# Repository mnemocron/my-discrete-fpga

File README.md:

# Discrete 7400 logic based FPGA
A custom, modular FPGA architecture simulated in VHDL (GHDL), realized with discrete 7400-logic ICs, layouted on PCB with KiCAD and programmed through an abstraction layer via Arduino.

---

Read the full thorugh process and many explanations on my blog: 
[mnemocron.github.io](https://mnemocron.github.io/2023-12-08-DIY-FPGA-diary-0/)

## Motivation

> Why build arguably the worst FPGA ever?

Ever since building Ben Eaters [8 bit CPU](https://eater.net/8bit) myself, I wanted to build something even crazier.
The 8 bit CPU is arguably the worst CPU ever built - but it is a fantastic educational example.
And that is the case for the **4 bit FPGA**. It is a purely educational side project that boosted my knowledge about FPGA architecture, VHDL design and verification. Without further ado, here it is.

## Build Process

The actual part list is WIP. Expected material cost are approximately 50 USD per assembled tile (4:4 bit LUT with interconnect).

---

## Start Here!

Do you want to build this FPGA yourself? Great! Everything, I made regarding this project is in this repository.

To understand the architecture start with `./architecture` or read about it on my blog.
Next, you may dive into the VHDL simulations in `./vhdl` and try out a few things.
Head straight to the `./vhdl/test` directory to see examples with the full FPGA architecture (instead of sub units).

- `./architecture` contains conceptual draw.io block diagrams
- `./doc` contains images, notes and tools that may be helpful
- `./ihdl` (WIP) contains ideas and concepts for a "compiler"
- `./kicad` contains **schematics and PCB files** for KiCAD 7.0
- `./sketch` contains Arduino code for testing of assembled PCB hardware and **abstraction layer in C**
- `./vhdl` contains models for 74xx ICs and the **full FPGA architecture for simulation**

---

## "Assemble" code to map onto the FPGA in Arduino

---

## Inspiration & Honorable Mentions

### Build an 8-bit computer from scratch

> I built a programmable 8-bit computer from scratch on breadboards using only simple logic gates. I documented the whole project in a series of YouTube videos and on this web site. Watch this video for an introduction:

on [eater.net](https://eater.net/8bit)

### Build your own FPGA

> Building a microcontroller or CPU out of discrete logic is a popular hobbyist pursuit, and it serves a useful purpose: building a CPU from scratch teaches you a lot about CPU architecture and tradeoffs; it's an interesting and instructive exercise. So, I wondered, wouldn't building an FPGA out of discrete logic be similarly educational? 

on [Nick's Blog](http://blog.notdot.net/2012/10/Build-your-own-FPGA)

on [Hackaday](https://hackaday.com/2012/11/01/discrete-fpga-will-probably-win-the-7400-logic-competition/)

### Princeton Regonfigurable Gate Array

> Build your own FPGA Chip or embedded FPGA IP with Python, and enjoy a fully open-source, auto-generated CAD flow specifically for your custom FPGA.

on [github](https://github.com/PrincetonUniversity/prga)

on [princeton.edu](http://parallel.princeton.edu/prga/)

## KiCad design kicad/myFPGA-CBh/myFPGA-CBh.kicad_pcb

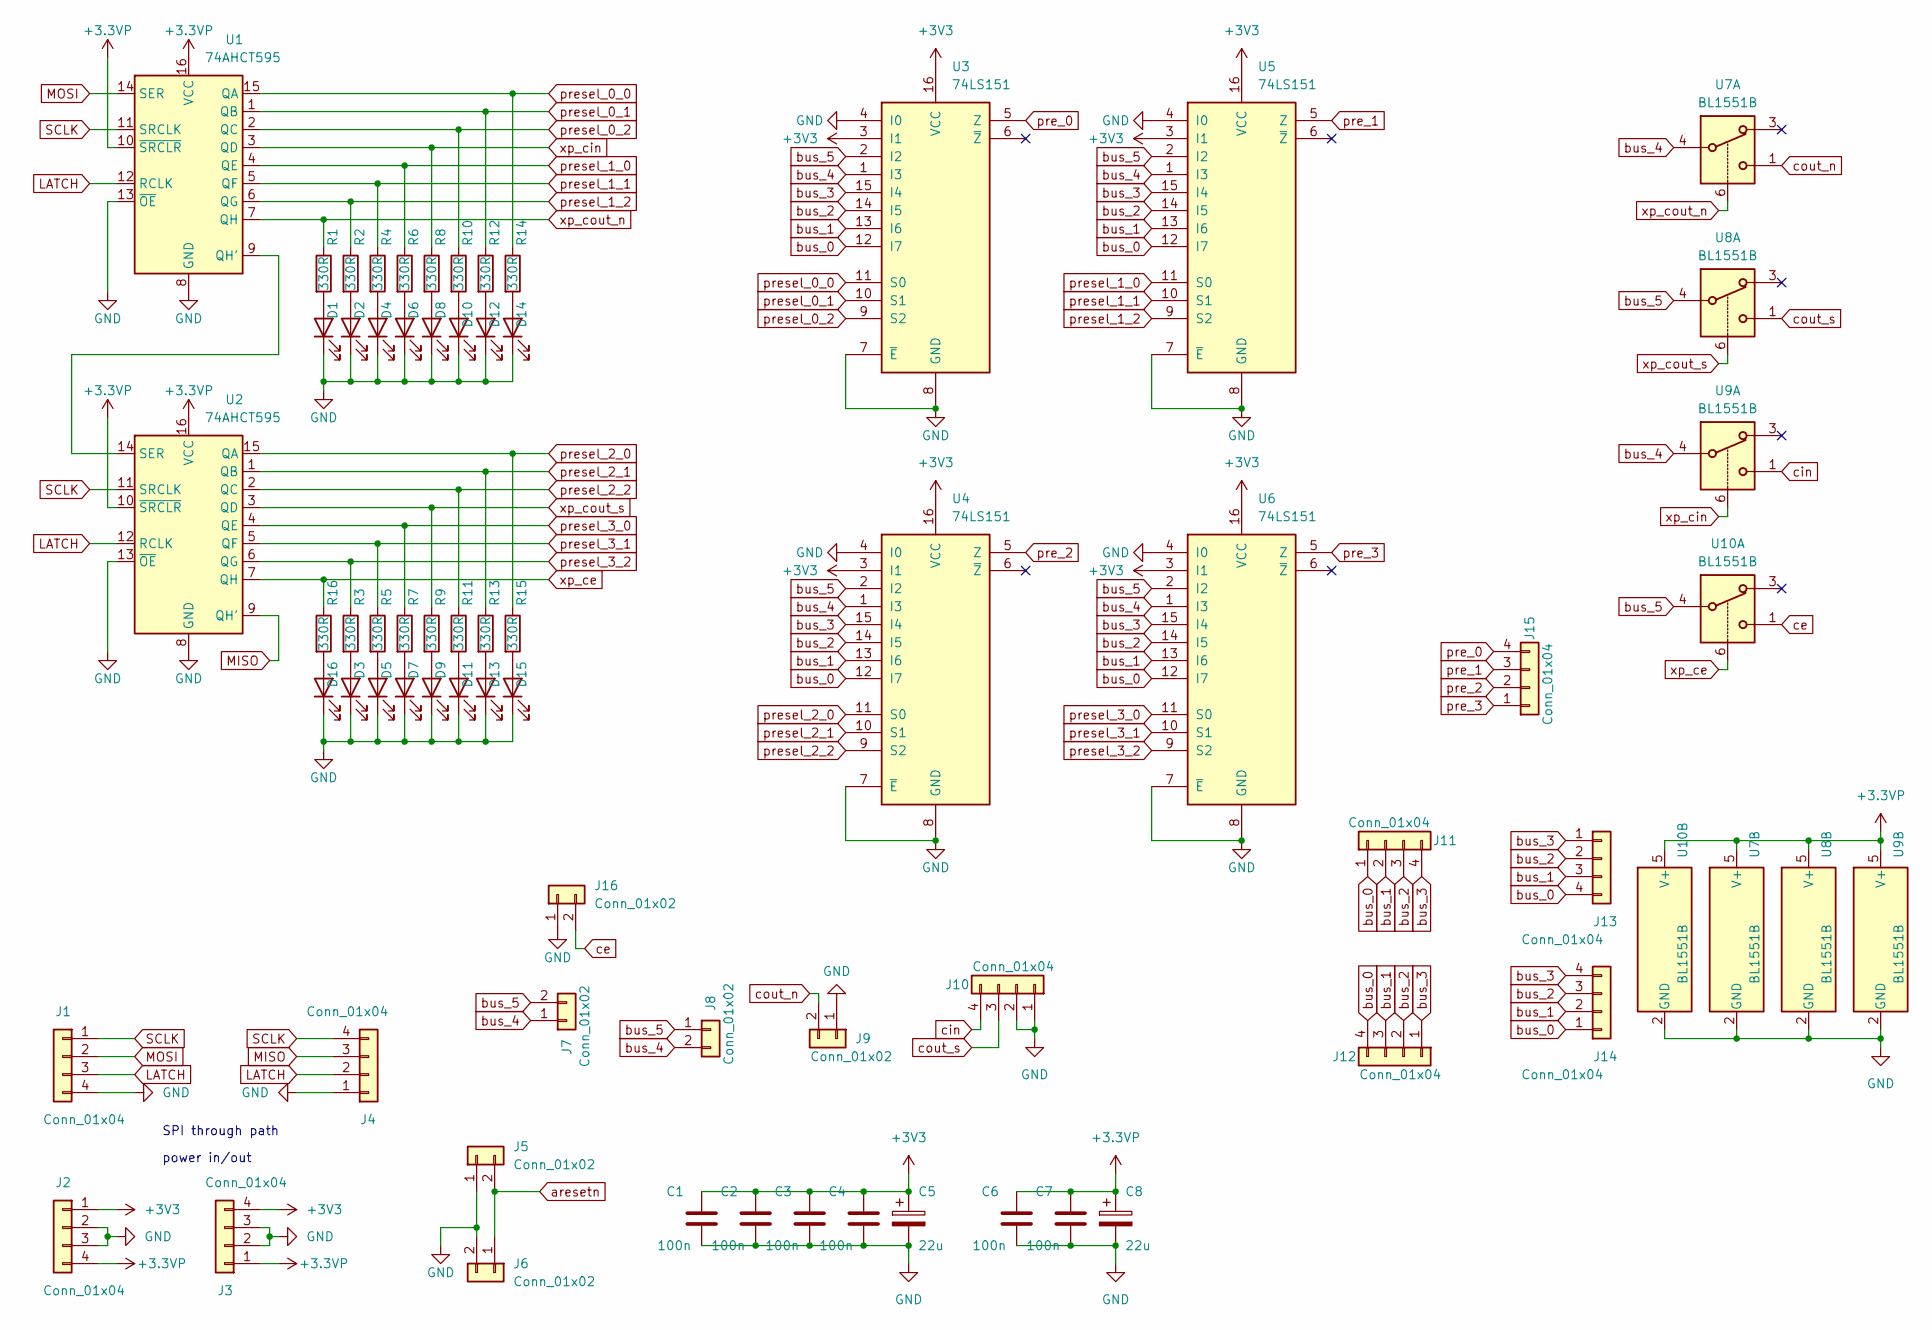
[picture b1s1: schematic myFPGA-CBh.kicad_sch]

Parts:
C1, C2, C3, C4, C6, C7: 100n; C_0603_1608Metric; Voltage 50; Part Nr. CC0603KRX7R9BB104; JLCPCB Part # C14663
C5, C8: 22u; R_1206_3216Metric; Voltage 25; Part Nr. CL31A226KAHNNNE; JLCPCB Part # C12891
D1, D2, D3, D4, D5, D6, D7, D8, D9, D10, D11, D12, D13, D14, D15, D16: LED (green); LED_0805_2012Metric; Part Nr. C2297; JLCPCB Part # C2297
J1, J2, J3, J4, J10, J11, J12, J13, J14, J15: Conn_01x04; PinHeader_1x04_P2.54mm_Horizontal; Part Nr. do not place; JLCPCB Part # do not place
J5, J6, J7, J8, J9, J16: Conn_01x02; PinHeader_1x02_P2.54mm_Horizontal; Part Nr. do not place; JLCPCB Part # do not place
R1, R2, R3, R4, R5, R6, R7, R8, R9, R10, R11, R12, R13, R14, R15, R16: 330R; R_0603_1608Metric; Part Nr. 0603WAF3300T5E; JLCPCB Part # C23138
U1, U2: 74AHCT595; SOIC-16_3.9x9.9mm_P1.27mm; Part Nr. 74HC595D; JLCPCB Part # C5947
U3, U4, U5, U6: 74LS151; SOIC-16_3.9x9.9mm_P1.27mm; Part Nr. 74HC151DR; JLCPCB Part # C6822
U7, U8, U9, U10: BL1551B; SOT-363_SC-70-6; Part Nr. BL1551B; JLCPCB Part # C2944066

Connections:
+3.3VP: C6.1, C7.1, C8.1, J2.4, J3.1, U1.10 (~SRCLR), U1.16 (VCC), U2.10 (~SRCLR), U2.16 (VCC), U7.5 (V+), U8.5 (V+), U9.5 (V+), U10.5 (V+)
+3V3: C1.1, C2.1, C3.1, C4.1, C5.1, J2.1, J3.4, U3.3 (I1), U3.16 (VCC), U4.3 (I1), U4.16 (VCC), U5.3 (I1), U5.16 (VCC), U6.3 (I1), U6.16 (VCC)
GND: C1.2, C2.2, C3.2, C4.2, C5.2, C6.2, C7.2, C8.2, D1.1 (K), D2.1 (K), D3.1 (K), D4.1 (K), D5.1 (K), D6.1 (K), D7.1 (K), D8.1 (K), D9.1 (K), D10.1 (K), D11.1 (K), D12.1 (K), D13.1 (K), D14.1 (K), D15.1 (K), D16.1 (K), J1.4, J2.2, J2.3, J3.2, J3.3, J4.1, J5.1, J6.2, J9.1, J10.1, J10.2, J16.1, U1.8 (GND), U1.13 (~OE), U2.8 (GND), U2.13 (~OE), U3.4 (I0), U3.7 (~E), U3.8 (GND), U4.4 (I0), U4.7 (~E), U4.8 (GND), U5.4 (I0), U5.7 (~E), U5.8 (GND), U6.4 (I0), U6.7 (~E), U6.8 (GND), U7.2 (GND), U8.2 (GND), U9.2 (GND), U10.2 (GND); also elsewhere on the board
LATCH: J1.3, J4.2, U1.12 (RCLK), U2.12 (RCLK); also elsewhere on the board
MISO: J4.3, U2.9 (QH'); also elsewhere on the board
MOSI: J1.2, U1.14 (SER)
unnamed: D1.2 (A), R1.2
unnamed: D2.2 (A), R2.2
unnamed: D3.2 (A), R3.2
unnamed: D4.2 (A), R4.2
unnamed: D5.2 (A), R5.2
unnamed 11: D6.2 (A), R6.2; also elsewhere on the board
unnamed: D7.2 (A), R7.2
unnamed: D8.2 (A), R8.2
unnamed: D9.2 (A), R9.2
unnamed: D10.2 (A), R10.2
unnamed: D11.2 (A), R11.2
unnamed: D12.2 (A), R12.2
unnamed: D13.2 (A), R13.2
unnamed: D14.2 (A), R14.2
unnamed: D15.2 (A), R15.2
unnamed: D16.2 (A), R16.2
unnamed: U1.9 (QH'), U2.14 (SER)
SCLK: J1.1, J4.4, U1.11 (SRCLK), U2.11 (SRCLK); also elsewhere on the board
aresetn: J5.2, J6.1; also elsewhere on the board
bus_0: J11.1, J12.4, J13.4, J14.1, U3.12 (I7), U4.12 (I7), U5.12 (I7), U6.12 (I7)
bus_1: J11.2, J12.3, J13.3, J14.2, U3.13 (I6), U4.13 (I6), U5.13 (I6), U6.13 (I6)
bus_2: J11.3, J12.2, J13.2, J14.3, U3.14 (I5), U4.14 (I5), U5.14 (I5), U6.14 (I5)
bus_3: J11.4, J12.1, J13.1, J14.4, U3.15 (I4), U4.15 (I4), U5.15 (I4), U6.15 (I4)
bus_4: J7.1, J8.2, U3.1 (I3), U4.1 (I3), U5.1 (I3), U6.1 (I3), U7.4, U9.4
bus_5: J7.2, J8.1, U3.2 (I2), U4.2 (I2), U5.2 (I2), U6.2 (I2), U8.4, U10.4
ce: J16.2, U10.1
cin: J10.4, U9.1; also elsewhere on the board
cout_n: J9.2, U7.1
cout_s: J10.3, U8.1; also elsewhere on the board
pre_0: J15.4, U3.5 (Z); also elsewhere on the board
pre_1: J15.3, U5.5 (Z); also elsewhere on the board
pre_2: J15.2, U4.5 (Z); also elsewhere on the board
pre_3: J15.1, U6.5 (Z); also elsewhere on the board
presel_0_0: R14.1, U1.15 (QA), U3.11 (S0)
presel_0_1: R12.1, U1.1 (QB), U3.10 (S1)
presel_0_2: R10.1, U1.2 (QC), U3.9 (S2)
presel_1_0: R6.1, U1.4 (QE), U5.11 (S0); also elsewhere on the board
presel_1_1: R4.1, U1.5 (QF), U5.10 (S1)
presel_1_2: R2.1, U1.6 (QG), U5.9 (S2)
presel_2_0: R15.1, U2.15 (QA), U4.11 (S0)
presel_2_1: R13.1, U2.1 (QB), U4.10 (S1)
presel_2_2: R11.1, U2.2 (QC), U4.9 (S2)
presel_3_0: R7.1, U2.4 (QE), U6.11 (S0)
presel_3_1: R5.1, U2.5 (QF), U6.10 (S1)
presel_3_2: R3.1, U2.6 (QG), U6.9 (S2)
xp_ce: R16.1, U2.7 (QH), U10.6
xp_cin: R8.1, U1.3 (QD), U9.6
xp_cout_n: R1.1, U1.7 (QH), U7.6
xp_cout_s: R9.1, U2.3 (QD), U8.6

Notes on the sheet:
SPI through path
power in/out

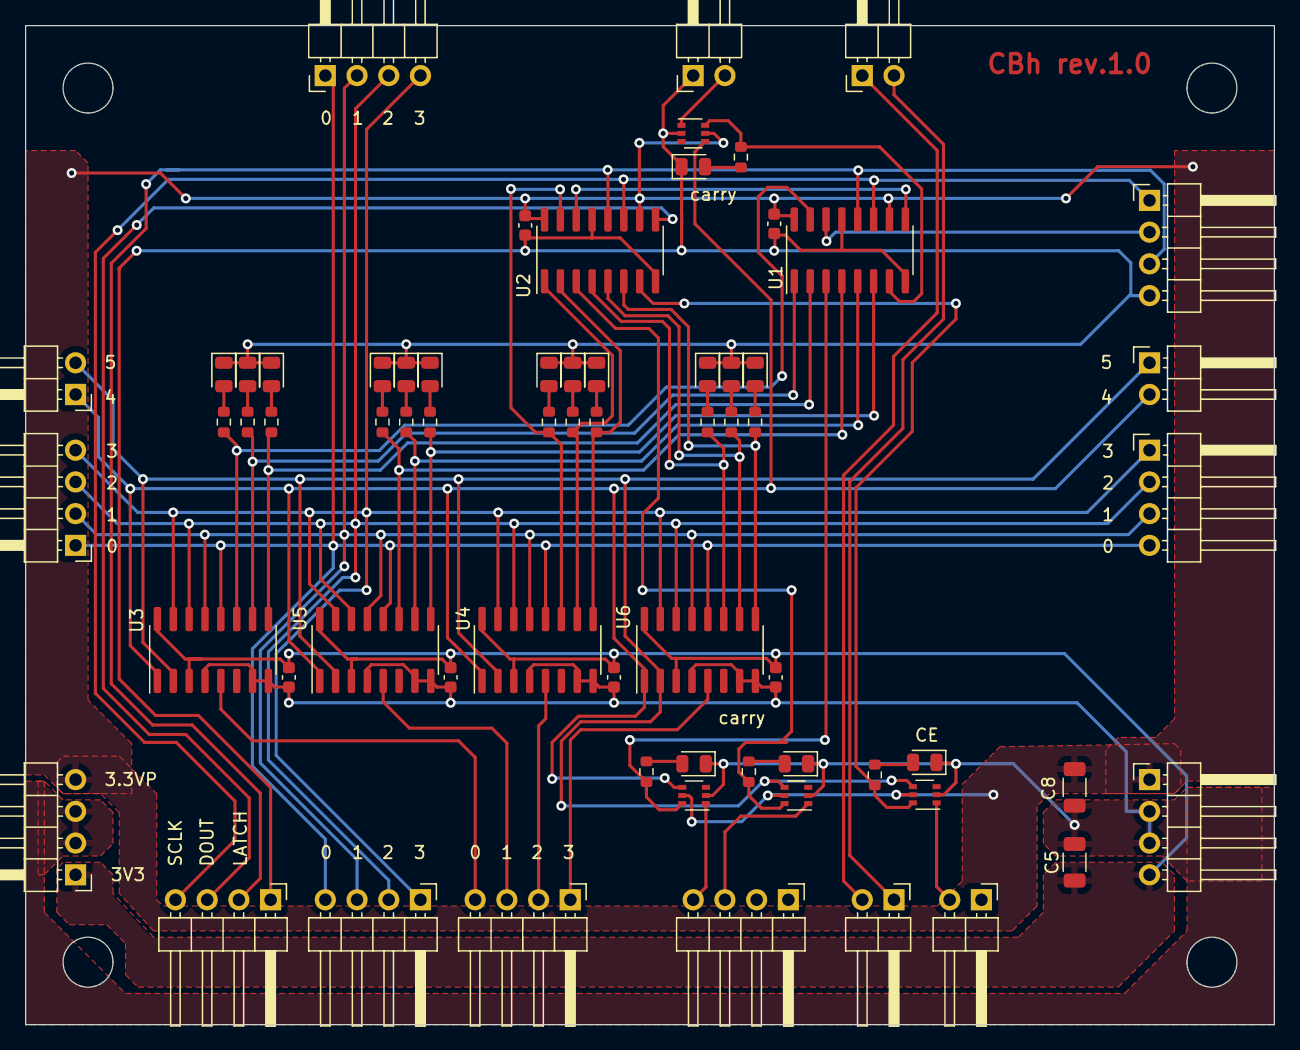
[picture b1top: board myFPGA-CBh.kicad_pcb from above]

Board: 2 copper layers, 100.0 x 80.0 mm, 66 parts (0 on the bottom side), 55 nets.

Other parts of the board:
Re: 330R; R_0603_1608Metric
locked: Conn_01x04; PinHeader_1x04_P2.54mm_Horizontal
locked#2: Conn_01x02; PinHeader_1x02_P2.54mm_Horizontal
locked#3, locked#4: Conn_01x04; PinHeader_1x04_P2.54mm_Horizontal

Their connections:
GND: locked.1, locked.2, locked#2.1, locked#4.1; also elsewhere on the board
LATCH: locked#4.2; also elsewhere on the board
MISO: locked#4.3; also elsewhere on the board
unnamed 11: Re.2; also elsewhere on the board
SCLK: locked#4.4; also elsewhere on the board
aresetn: locked#2.2; also elsewhere on the board
cin: locked.4; also elsewhere on the board
cout_s: locked.3; also elsewhere on the board
pre_0: locked#3.4; also elsewhere on the board
pre_1: locked#3.3; also elsewhere on the board
pre_2: locked#3.2; also elsewhere on the board
pre_3: locked#3.1; also elsewhere on the board
presel_1_0: Re.1; also elsewhere on the board

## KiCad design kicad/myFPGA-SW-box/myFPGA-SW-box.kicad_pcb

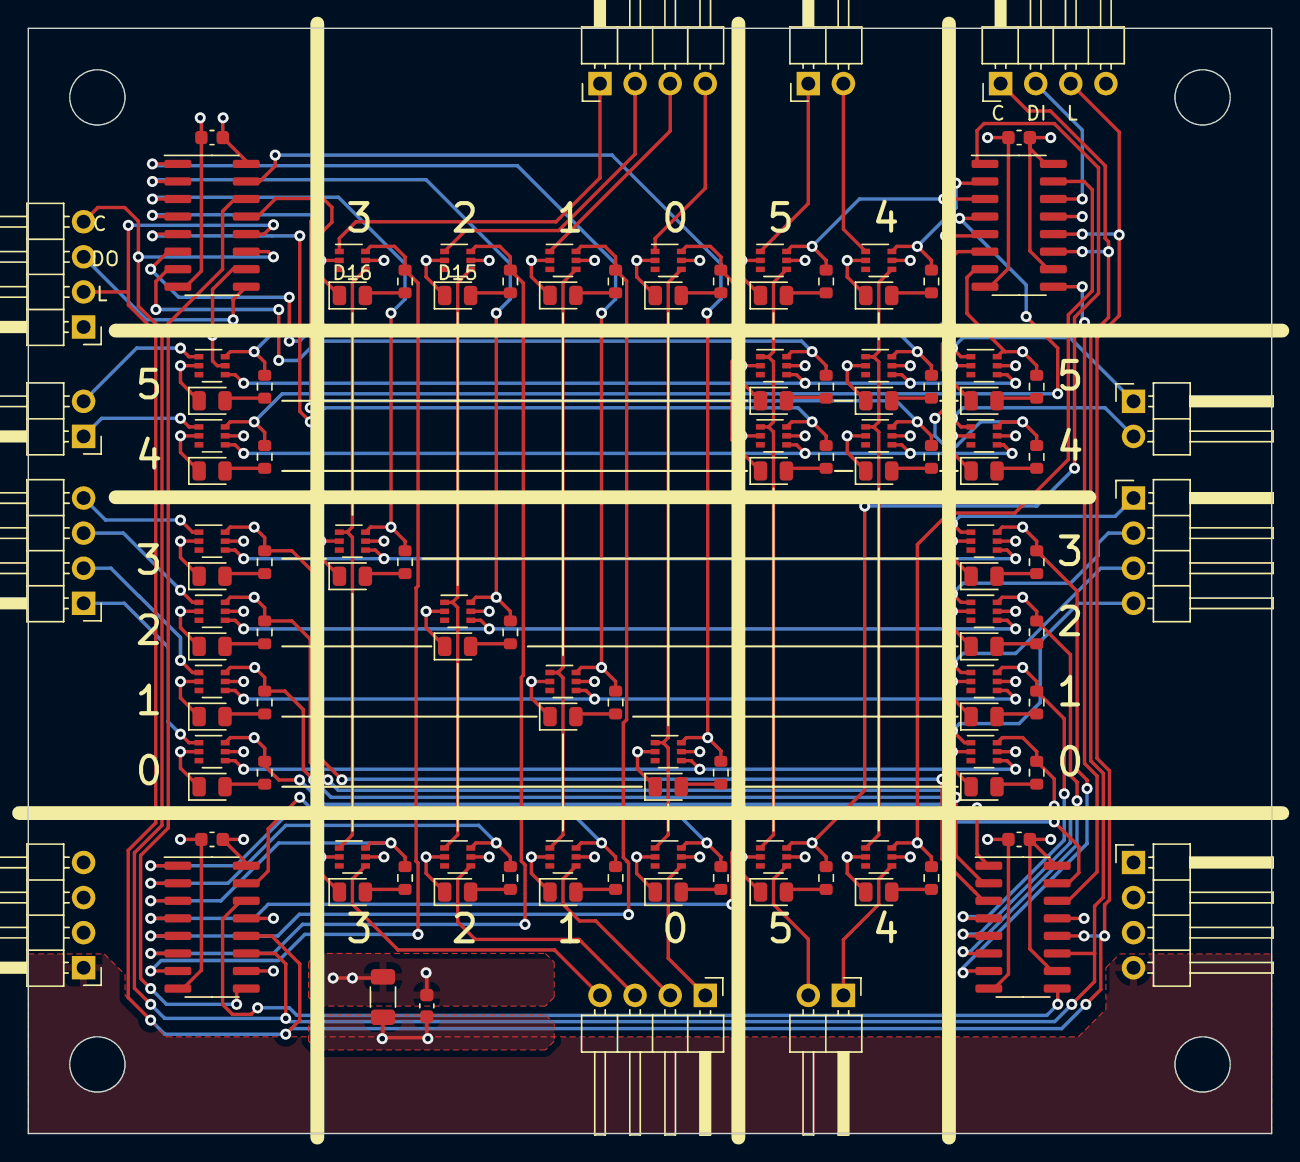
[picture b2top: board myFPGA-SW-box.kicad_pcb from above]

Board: 4 copper layers, 90.0 x 80.0 mm, 118 parts (0 on the bottom side), 110 nets.

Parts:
C1, C2, C3, C4, C5: 100n; C_0603_1608Metric
C6: 22u; R_1206_3216Metric
D1, D2, D3, D4, D5, D6, D7, D8, D9, D10, D11, D12, D13, D14, D15, D16, D17, D18, D19, D20, D21, D22, D23, D24, D25, D26, D27, D28, D29, D30, D31, D32: LED (green); LED_0805_2012Metric
J1, J2, J3, J4, J5, J6, J7, J9: Conn_01x04; PinHeader_1x04_P2.54mm_Horizontal
J8, J10, J11, J12: Conn_01x02; PinHeader_1x02_P2.54mm_Horizontal
R1, R2, R3, R4, R5, R6, R7, R8, R9, R10, R11, R12, R13, R14, R15, R16, R18, R19, R20, R21, R22, R23, R24, R25, R26, R27, R28, R29, R30, R31, R32: 10k; R_0603_1608Metric
Re: 10k; R_0603_1608Metric
U1, U2, U3, U4: 74HC595; SOIC-16_3.9x9.9mm_P1.27mm
U5, U6, U7, U8, U9, U10, U11, U12, U13, U14, U15, U16, U17, U18, U19, U20, U21, U22, U23, U24, U25, U26, U27, U28, U29, U30, U31, U32, U33, U34, U35, U36: NC7SB3157P6X; SOT-363_SC-70-6

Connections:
+3.3VP: C1.1, C2.1, C3.1, C4.1, C5.1, C6.1, J7.4, J9.1, U1.10 (~SRCLR), U1.16 (VCC), U2.10 (~SRCLR), U2.16 (VCC), U3.10 (~SRCLR), U3.16 (VCC), U4.10 (~SRCLR), U4.16 (VCC), U5.5 (V+), U6.5 (V+), U7.5 (V+), U8.5 (V+), U9.5 (V+), U10.5 (V+), U11.5 (V+), U12.5 (V+), U13.5 (V+), U14.5 (V+), U15.5 (V+), U16.5 (V+), U17.5 (V+), U18.5 (V+), U19.5 (V+), U20.5 (V+), U21.5 (V+), U22.5 (V+), U23.5 (V+), U24.5 (V+), U25.5 (V+), U26.5 (V+), U27.5 (V+), U28.5 (V+), U29.5 (V+), U30.5 (V+), U31.5 (V+), U32.5 (V+), U33.5 (V+), U34.5 (V+), U35.5 (V+), U36.5 (V+)
+3V3: J7.1, J9.4
/east_0: J6.4, U24.1
/east_1: J6.3, U23.1
/east_2: J6.2, U22.1
/east_3: J6.1, U21.1
/north_0: J5.4, U19.1
/north_1: J5.3, U16.1
/north_2: J5.2, U13.1
/north_3: J5.1, U10.1
/prio_east_0: J12.2, U36.1
/prio_east_1: J12.1, U35.1
/prio_north_0: J10.2, U31.1
/prio_north_1: J10.1, U27.1
/prio_south_0: J11.1, U34.4
/prio_south_1: J11.2, U30.4
/prio_west_0: J8.1, U26.1
/prio_west_1: J8.2, U25.1
/south_0: J4.1, U20.4
/south_1: J4.2, U17.4
/south_2: J4.3, U14.4
/south_3: J4.4, U11.4
/west_0: J3.1, U8.1
/west_1: J3.2, U7.1
/west_2: J3.3, U6.1
/west_3: J3.4, U5.1
GND: C1.2, C2.2, C3.2, C4.2, C5.2, C6.2, D1.1 (K), D2.1 (K), D3.1 (K), D4.1 (K), D5.1 (K), D6.1 (K), D7.1 (K), D8.1 (K), D9.1 (K), D10.1 (K), D11.1 (K), D12.1 (K), D13.1 (K), D14.1 (K), D15.1 (K), D16.1 (K), D17.1 (K), D18.1 (K), D19.1 (K), D20.1 (K), D21.1 (K), D22.1 (K), D23.1 (K), D24.1 (K), D25.1 (K), D26.1 (K), D27.1 (K), D28.1 (K), D29.1 (K), D30.1 (K), D31.1 (K), D32.1 (K), J1.4, J2.1, J7.2, J7.3, J9.2, J9.3, U1.8 (GND), U1.13 (~OE), U2.8 (GND), U2.13 (~OE), U3.8 (GND), U3.13 (~OE), U4.8 (GND), U4.13 (~OE), U5.2 (GND), U6.2 (GND), U7.2 (GND), U8.2 (GND), U9.2 (GND), U10.2 (GND), U11.2 (GND), U12.2 (GND), U13.2 (GND), U14.2 (GND), U15.2 (GND), U16.2 (GND), U17.2 (GND), U18.2 (GND), U19.2 (GND), U20.2 (GND), U21.2 (GND), U22.2 (GND), U23.2 (GND), U24.2 (GND), U25.2 (GND), U26.2 (GND), U27.2 (GND), U28.2 (GND), U29.2 (GND), U30.2 (GND), U31.2 (GND), U32.2 (GND), U33.2 (GND), U34.2 (GND), U35.2 (GND), U36.2 (GND)
LATCH: J1.3, J2.2, U1.12 (RCLK), U2.12 (RCLK), U3.12 (RCLK), U4.12 (RCLK)
MISO: J2.3, U4.9 (QH')
MOSI: J1.2, U1.14 (SER)
unnamed: D1.2 (A), R1.2
unnamed: D2.2 (A), R2.2
unnamed: D3.2 (A), R3.2
unnamed: D4.2 (A), R4.2
unnamed: D5.2 (A), R5.2
unnamed: D6.2 (A), R6.2
unnamed: D7.2 (A), R7.2
unnamed: D8.2 (A), R8.2
unnamed: D9.2 (A), R9.2
unnamed: D10.2 (A), R10.2
unnamed: D11.2 (A), R11.2
unnamed: D12.2 (A), R12.2
unnamed: D13.2 (A), R13.2
unnamed: D14.2 (A), R14.2
unnamed: D15.2 (A), R15.2
unnamed: D16.2 (A), R16.2
unnamed: D17.2 (A), Re.2
unnamed: D18.2 (A), R18.2
unnamed: D19.2 (A), R19.2
unnamed: D20.2 (A), R20.2
unnamed: D21.2 (A), R21.2
unnamed: D22.2 (A), R22.2
unnamed: D23.2 (A), R23.2
unnamed: D24.2 (A), R24.2
unnamed: D25.2 (A), R25.2
unnamed: D26.2 (A), R26.2
unnamed: D27.2 (A), R27.2
unnamed: D28.2 (A), R28.2
unnamed: D29.2 (A), R29.2
unnamed: D30.2 (A), R30.2
unnamed: D31.2 (A), R31.2
unnamed: D32.2 (A), R32.2
unnamed: U1.9 (QH'), U2.14 (SER)
unnamed: U2.9 (QH'), U3.14 (SER)
unnamed: U3.9 (QH'), U4.14 (SER)
unnamed: U9.1, U10.4, U11.1
unnamed: U12.1, U13.4, U14.1
unnamed: U6.4, U12.4, U22.4
unnamed: U15.1, U16.4, U17.1
unnamed: U7.4, U15.4, U23.4
unnamed: U18.1, U19.4, U20.1
unnamed: U8.4, U18.4, U24.4
unnamed: U5.4, U9.4, U21.4
unnamed: U25.4, U28.4, U32.4, U35.4
unnamed: U26.4, U29.4, U33.4, U36.4
unnamed: U27.4, U28.1, U29.1, U30.1
unnamed: U31.4, U32.1, U33.1, U34.1
SCLK: J1.1, J2.4, U1.11 (SRCLK), U2.11 (SRCLK), U3.11 (SRCLK), U4.11 (SRCLK)
sw_8: R9.1, U3.15 (QA), U20.6
sw_9: R10.1, U3.1 (QB), U17.6
sw_10: R11.1, U3.2 (QC), U14.6
sw_11: R12.1, U3.3 (QD), U11.6
sw_12: R13.1, U3.4 (QE), U19.6
sw_13: R14.1, U3.5 (QF), U16.6
sw_14: R15.1, U3.6 (QG), U13.6
sw_15: R16.1, U3.7 (QH), U10.6
sw_16: R25.1, U2.15 (QA), U8.6
sw_17: R26.1, U2.1 (QB), U7.6
sw_18: R27.1, U2.2 (QC), U6.6
sw_19: R28.1, U2.3 (QD), U5.6
sw_20: R29.1, U2.4 (QE), U24.6
sw_21: R30.1, U2.5 (QF), U23.6
sw_22: R31.1, U2.6 (QG), U22.6
sw_23: R32.1, U2.7 (QH), U21.6
sw_24: Re.1, U1.15 (QA), U34.6
sw_25: R18.1, U1.1 (QB), U30.6
sw_26: R19.1, U1.2 (QC), U31.6
sw_27: R20.1, U1.3 (QD), U27.6
sw_28: R21.1, U1.4 (QE), U26.6
sw_29: R22.1, U1.5 (QF), U25.6
sw_30: R23.1, U1.6 (QG), U36.6
sw_31: R24.1, U1.7 (QH), U35.6
xp_0: R1.1, U4.15 (QA), U18.6
xp_1: R2.1, U4.1 (QB), U15.6
xp_2: R3.1, U4.2 (QC), U12.6
xp_3: R4.1, U4.3 (QD), U9.6
xp_4: R5.1, U4.4 (QE), U33.6
xp_5: R6.1, U4.5 (QF), U29.6
xp_6: R7.1, U4.6 (QG), U32.6
xp_7: R8.1, U4.7 (QH), U28.6

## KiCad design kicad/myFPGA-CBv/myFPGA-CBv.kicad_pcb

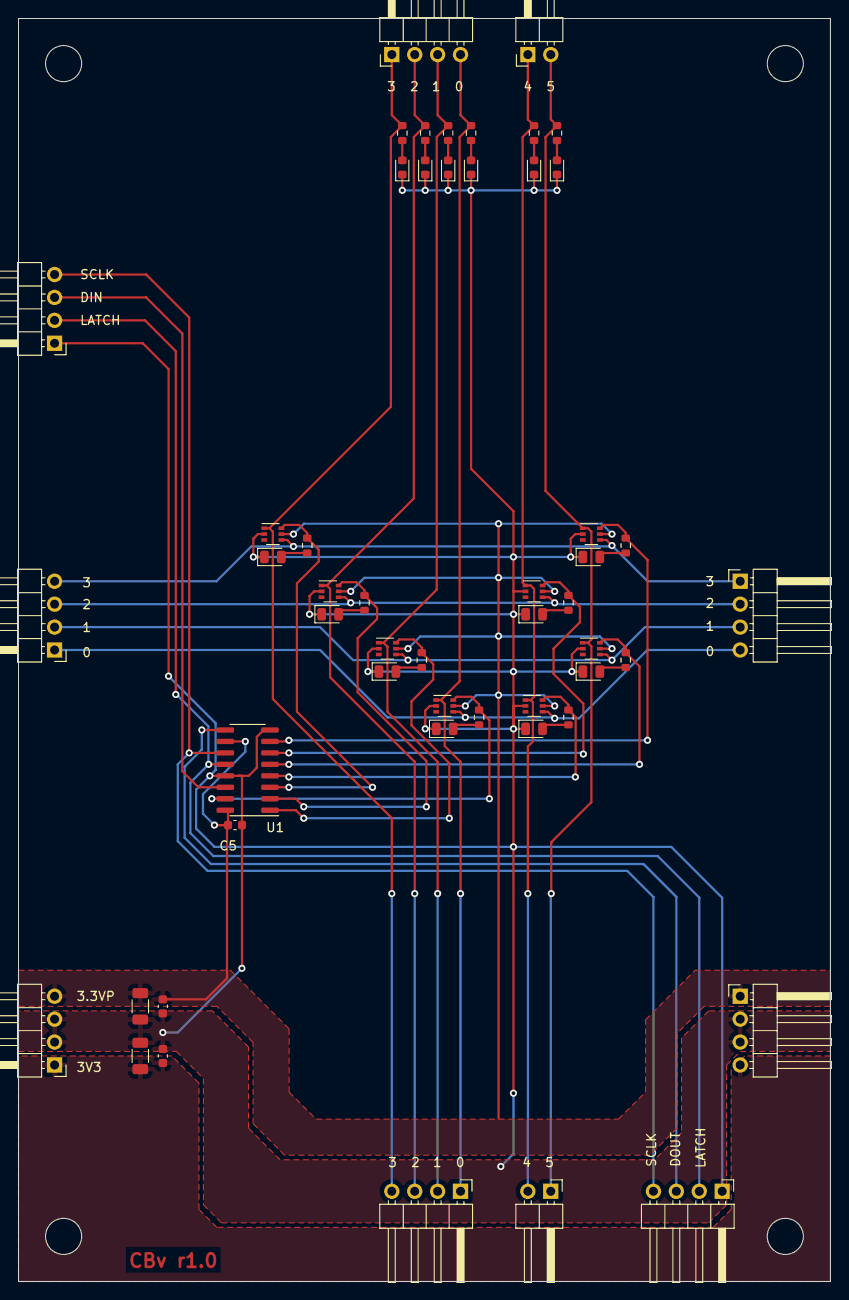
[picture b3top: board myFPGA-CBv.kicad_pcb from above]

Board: 2 copper layers, 90.0 x 140.0 mm, 52 parts (0 on the bottom side), 39 nets.

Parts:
C1, C3, C5: 100n; C_0603_1608Metric
C2, C4: 22u; R_1206_3216Metric
D1, D2, D3, D4, D5, D6, D7, D8: LED (green); LED_0805_2012Metric
D9, D10, D11, D12, D13, D14: LED (blue); LED_0603_1608Metric
J1, J2, J3, J4, J7, J8, J9, J10: Conn_01x04; PinHeader_1x04_P2.54mm_Horizontal
J5, J6: Conn_01x02; PinHeader_1x02_P2.54mm_Horizontal
R1, R2, R3, R4, R5, R6, R7, R8, R9, R10, R11, R12, R13, R14: 10k; R_0603_1608Metric
U1: 74HC595; SOIC-16_3.9x9.9mm_P1.27mm
U2, U3, U4, U5, U6, U7, U8, U9: NC7SB3157P6X; SOT-363_SC-70-6

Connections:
+3.3VP: C1.1, C2.1, C5.1, J1.4, J7.1, U1.10 (~SRCLR), U1.16 (VCC), U2.5 (V+), U3.5 (V+), U4.5 (V+), U5.5 (V+), U6.5 (V+), U7.5 (V+), U8.5 (V+), U9.5 (V+)
+3V3: C3.1, C4.1, J1.1, J7.4
/s_0: J2.1, J8.4, U5.4, U8.4
/s_1: J2.2, J8.3, U4.4, U7.4
/s_2: J2.3, J8.2, U3.4, U6.4
/s_3: J2.4, J8.1, U2.4, U9.4
GND: C1.2, C2.2, C3.2, C4.2, C5.2, D1.1 (K), D2.1 (K), D3.1 (K), D4.1 (K), D5.1 (K), D6.1 (K), D7.1 (K), D8.1 (K), D9.1 (K), D10.1 (K), D11.1 (K), D12.1 (K), D13.1 (K), D14.1 (K), J1.2, J1.3, J7.2, J7.3, J9.1, J10.1, U1.8 (GND), U1.13 (~OE), U2.2 (GND), U3.2 (GND), U4.2 (GND), U5.2 (GND), U6.2 (GND), U7.2 (GND), U8.2 (GND), U9.2 (GND)
LATCH: J9.2, J10.2, U1.12 (RCLK)
MISO: J10.3, U1.9 (QH')
MOSI: J9.3, U1.14 (SER)
unnamed: D1.2 (A), R1.2
unnamed: D2.2 (A), R2.2
unnamed: D3.2 (A), R3.2
unnamed: D4.2 (A), R4.2
unnamed: D5.2 (A), R5.2
unnamed: D6.2 (A), R6.2
unnamed: D7.2 (A), R7.2
unnamed: D8.2 (A), R8.2
unnamed: D9.2 (A), R9.2
unnamed: D10.2 (A), R10.2
unnamed: D11.2 (A), R11.2
unnamed: D12.2 (A), R12.2
unnamed: D13.2 (A), R13.2
unnamed: D14.2 (A), R14.2
SCLK: J9.4, J10.4, U1.11 (SRCLK)
bus_0: J3.1, J4.4, R9.1, U5.1
bus_1: J3.2, J4.3, R10.1, U4.1
bus_2: J3.3, J4.2, R11.1, U3.1
bus_3: J3.4, J4.1, R12.1, U2.1
prio_0: J5.2, J6.1, R13.1, U7.1, U9.1
prio_1: J5.1, J6.2, R14.1, U6.1, U8.1
xp_0: R1.1, U1.15 (QA), U5.6
xp_1: R2.1, U1.1 (QB), U4.6
xp_2: R3.1, U1.2 (QC), U3.6
xp_3: R4.1, U1.3 (QD), U2.6
xp_4: R5.1, U1.4 (QE), U8.6
xp_5: R6.1, U1.5 (QF), U7.6
xp_6: R7.1, U1.6 (QG), U6.6
xp_7: R8.1, U1.7 (QH), U9.6

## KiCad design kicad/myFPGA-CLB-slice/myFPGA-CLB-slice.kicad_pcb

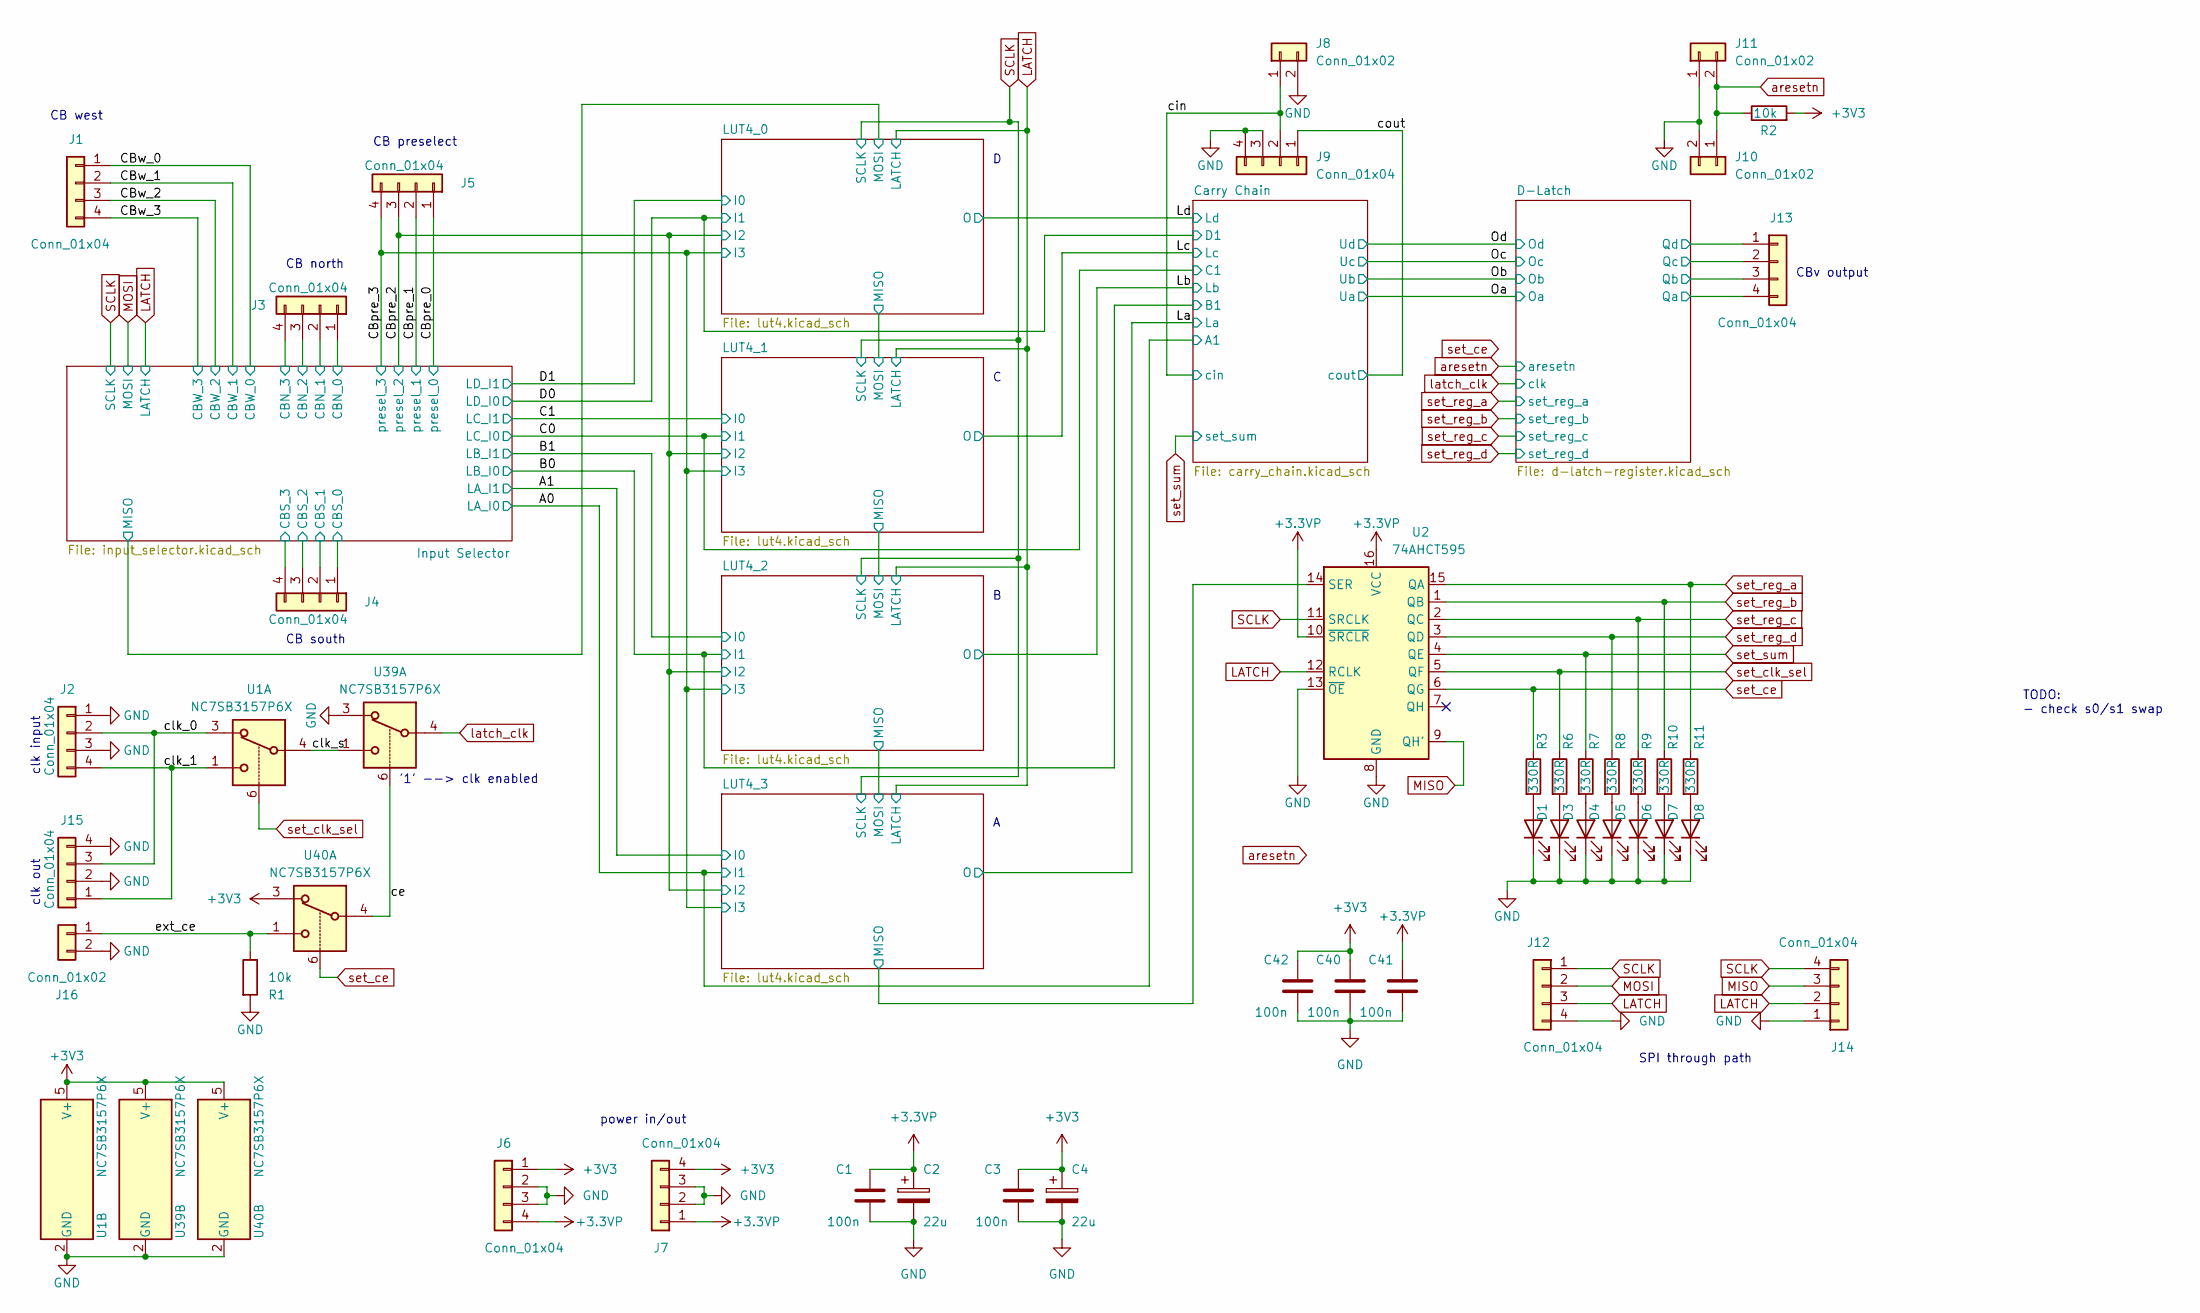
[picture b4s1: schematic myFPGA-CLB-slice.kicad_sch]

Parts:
C1, C3, C40, C41, C42: 100n; C_0603_1608Metric; Voltage 50; Part Nr. CC0603KRX7R9BB104; JLCPCB Part # C14663
C2, C4: 22u; R_1206_3216Metric; Voltage 25; Part Nr. CL31A226KAHNNNE; JLCPCB Part # C12891
D1, D3, D4, D5, D6, D7, D8: LED (green); LED_0805_2012Metric; Part Nr. C2297; JLCPCB Part # C2297
J1, J2, J3, J4, J5, J6, J7, J9, J12, J13, J14, J15: Conn_01x04; PinHeader_1x04_P2.54mm_Horizontal; Part Nr. do not place; JLCPCB Part # do not place
J8, J10, J11, J16: Conn_01x02; PinHeader_1x02_P2.54mm_Horizontal; Part Nr. do not place; JLCPCB Part # do not place
R1, R2: 10k; R_0603_1608Metric; Part Nr. 0603WAF1002T5E; JLCPCB Part # C25804
R3, R6, R7, R8, R9, R10, R11: 330R; R_0603_1608Metric; Part Nr. 0603WAF3300T5E; JLCPCB Part # C23138
U1, U39, U40: NC7SB3157P6X; SOT-363_SC-70-6; Part Nr. 74LVC1G157GW; JLCPCB Part # C135822
U2: 74AHCT595; SOIC-16_3.9x9.9mm_P1.27mm; Part Nr. 74HC595D; JLCPCB Part # C5947

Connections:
+3.3VP: C1.1, C2.1, C41.1, J6.4, J7.1, U2.10 (~SRCLR), U2.16 (VCC); also elsewhere on the board
+3V3: C3.1, C4.1, C40.1, C42.1, J6.1, J7.4, R2.2, U1.5 (V+), U39.5 (V+), U40.3, U40.5 (V+); also elsewhere on the board
/CBpre_0: J5.1; also elsewhere on the board
/CBpre_1: J5.2; also elsewhere on the board
/CBpre_2: J5.3; also elsewhere on the board
/CBpre_3: J5.4; also elsewhere on the board
/CBw_0: J1.1; also elsewhere on the board
/CBw_1: J1.2; also elsewhere on the board
/CBw_2: J1.3; also elsewhere on the board
/CBw_3: J1.4; also elsewhere on the board
/D-Latch/Qa: J13.4; also elsewhere on the board
/D-Latch/Qb: J13.3; also elsewhere on the board
/D-Latch/Qc: J13.2; also elsewhere on the board
/D-Latch/Qd: J13.1; also elsewhere on the board
/Input Selector/CBN_0: J3.1; also elsewhere on the board
/Input Selector/CBN_1: J3.2; also elsewhere on the board
/Input Selector/CBN_2: J3.3; also elsewhere on the board
/Input Selector/CBN_3: J3.4; also elsewhere on the board
/Input Selector/CBS_0: J4.1; also elsewhere on the board
/Input Selector/CBS_1: J4.2; also elsewhere on the board
/Input Selector/CBS_2: J4.3; also elsewhere on the board
/Input Selector/CBS_3: J4.4; also elsewhere on the board
/LUT4_3/MISO: U2.14 (SER); also elsewhere on the board
/ce: U39.6, U40.4
/cin: J8.1, J9.2; also elsewhere on the board
/clk_0: J2.2, J15.3, U1.3
/clk_1: J2.4, J15.1, U1.1
/clk_s: U1.4, U39.1
/cout: J9.1; also elsewhere on the board
/ext_ce: J16.1, R1.1, U40.1
GND: C1.2, C2.2, C3.2, C4.2, C40.2, C41.2, C42.2, D1.1 (K), D3.1 (K), D4.1 (K), D5.1 (K), D6.1 (K), D7.1 (K), D8.1 (K), J2.1, J2.3, J6.2, J6.3, J7.2, J7.3, J8.2, J9.3, J9.4, J10.2, J11.1, J12.4, J14.1, J15.2, J15.4, J16.2, R1.2, U1.2 (GND), U2.8 (GND), U2.13 (~OE), U39.2 (GND), U39.3, U40.2 (GND); also elsewhere on the board
LATCH: J12.3, J14.2, U2.12 (RCLK); also elsewhere on the board
MISO: J14.3, U2.9 (QH')
MOSI: J12.2; also elsewhere on the board
unnamed: D1.2 (A), R3.2
unnamed: D3.2 (A), R6.2
unnamed: D4.2 (A), R7.2
unnamed: D5.2 (A), R8.2
unnamed: D6.2 (A), R9.2
unnamed: D7.2 (A), R10.2
unnamed: D8.2 (A), R11.2
SCLK: J12.1, J14.4, U2.11 (SRCLK); also elsewhere on the board
aresetn: J10.1, J11.2, R2.1; also elsewhere on the board
latch_clk: U39.4; also elsewhere on the board
set_ce: R3.1, U2.6 (QG), U40.6
set_clk_sel: R6.1, U1.6, U2.5 (QF)
set_reg_a: R11.1, U2.15 (QA); also elsewhere on the board
set_reg_b: R10.1, U2.1 (QB); also elsewhere on the board
set_reg_c: R9.1, U2.2 (QC); also elsewhere on the board
set_reg_d: R8.1, U2.3 (QD); also elsewhere on the board
set_sum: R7.1, U2.4 (QE); also elsewhere on the board

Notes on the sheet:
clk input
CB south
CB preselect
CB north
clk out
CB west
'1' --> clk enabled
TODO: - check s0/s1 swap
CBv output
SPI through path
power in/out
